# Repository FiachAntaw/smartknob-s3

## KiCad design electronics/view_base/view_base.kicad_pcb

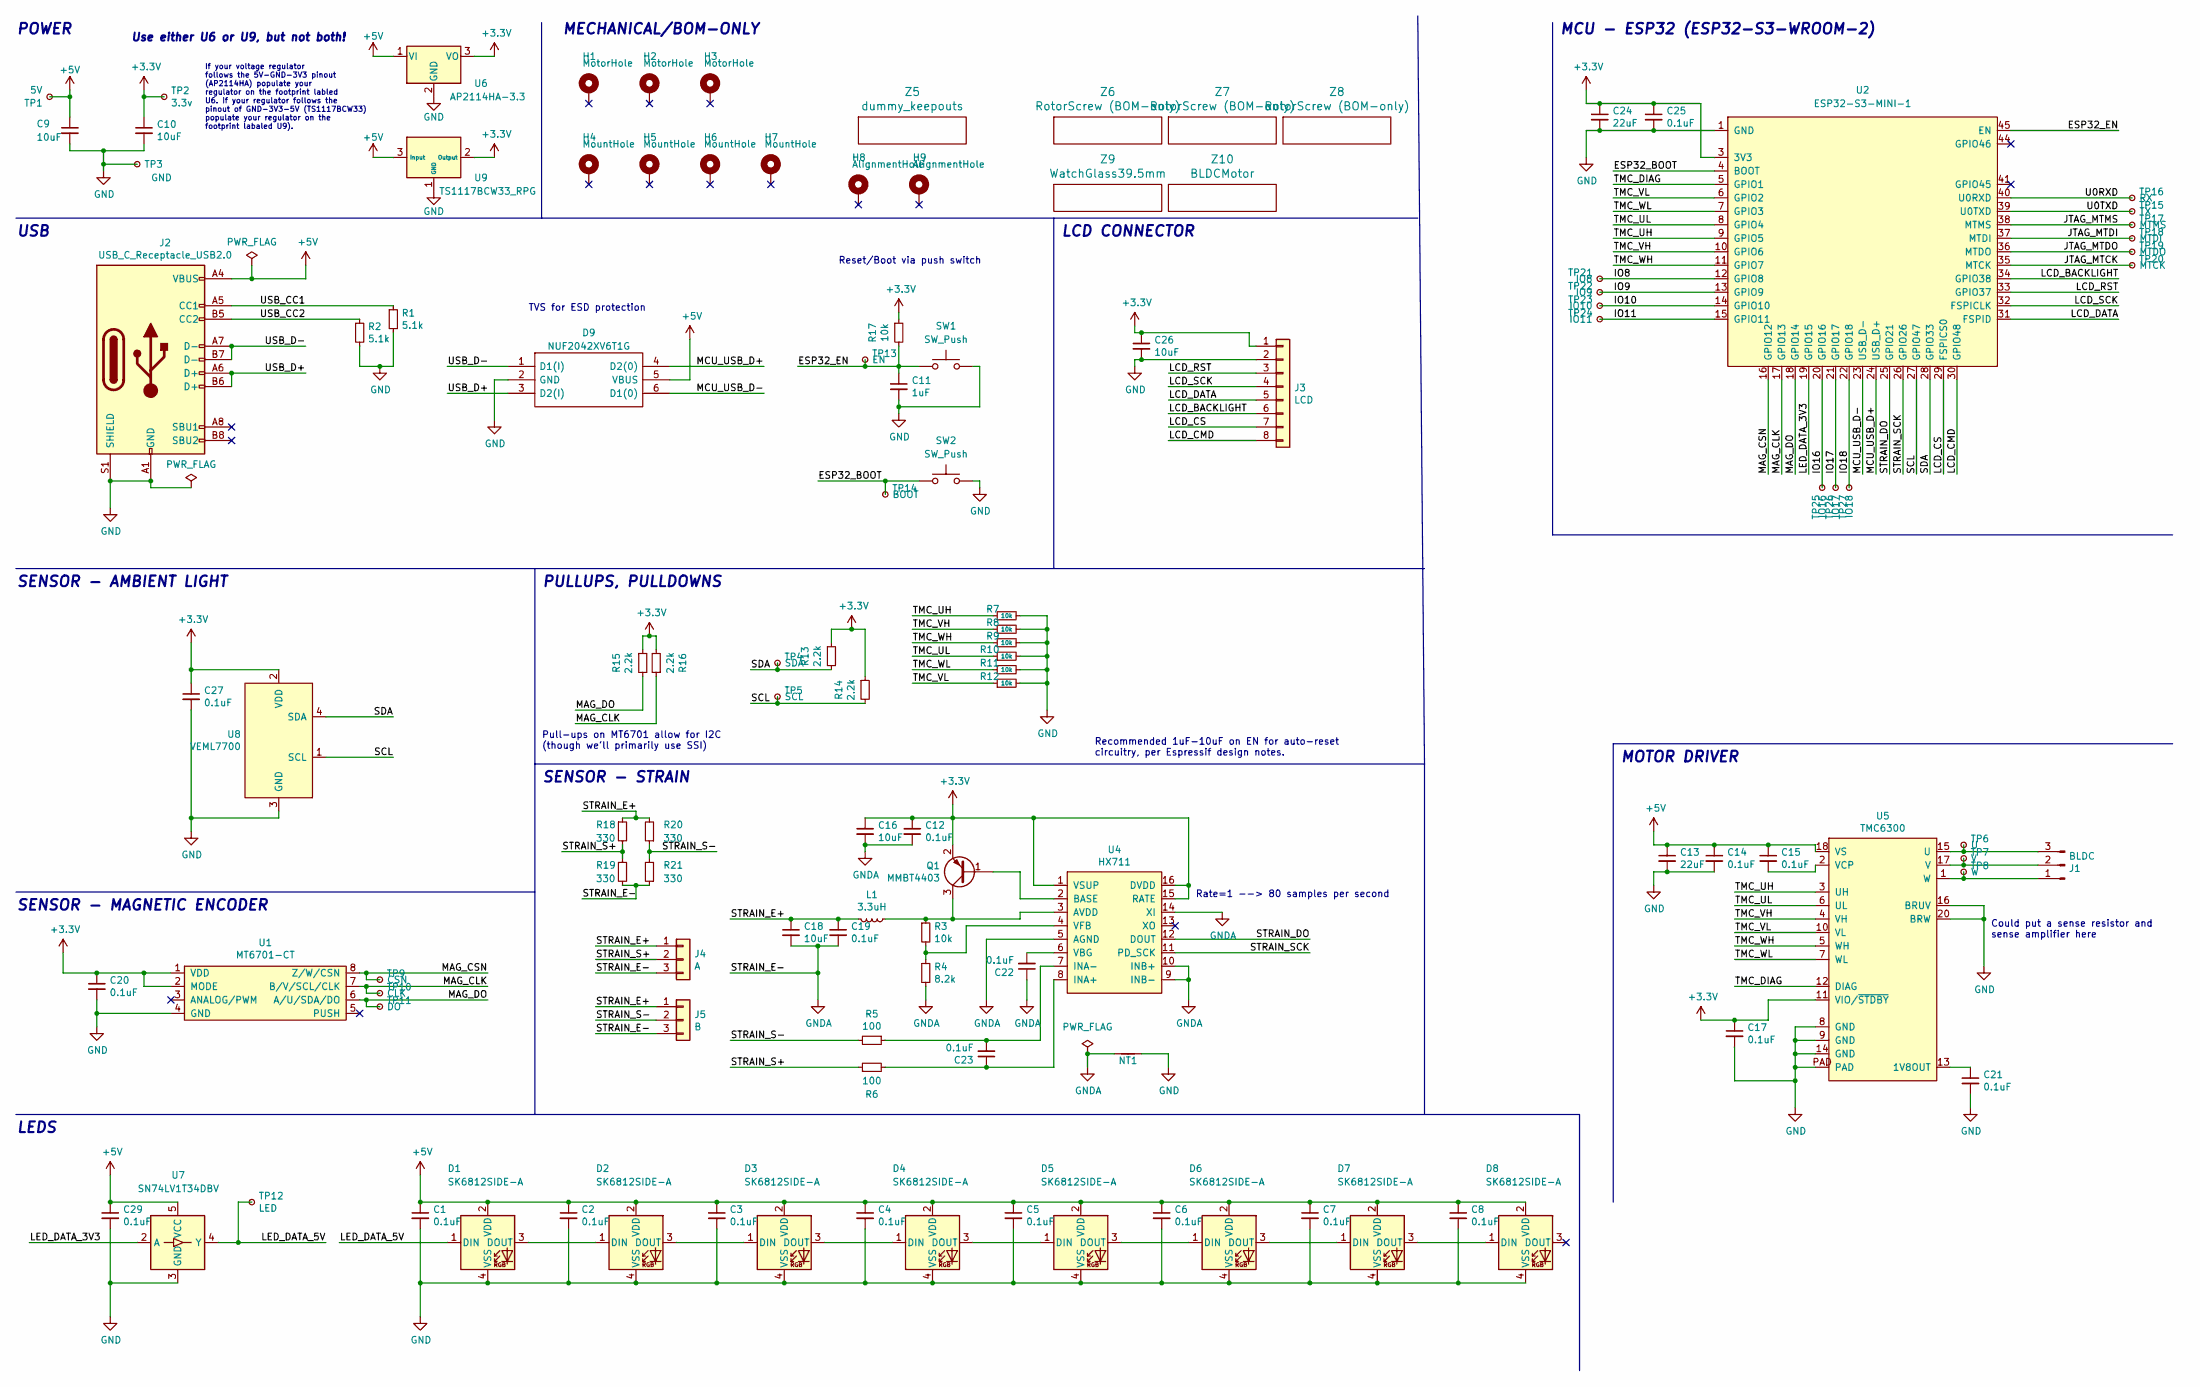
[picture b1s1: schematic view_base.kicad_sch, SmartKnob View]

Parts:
C1, C2, C3, C4, C5, C6, C7, C8, C12, C14, C15, C17, C19, C20, C21, C22, C23, C25, C27, C29: 0.1uF; C_0603_1608Metric; LCSC C1591
C9, C10, C16, C18, C26: 10uF; C_0805_2012Metric; LCSC C2922480
C11: 1uF; C_0603_1608Metric; Mouser 187-CL10A105KA8NNNC
C13, C24: 22uF; C_0805_2012Metric; LCSC C98190
D1, D2, D3, D4, D5, D6, D7, D8: SK6812SIDE-A; SK6812-SIDE-A; Digikey 1528-4691-ND
D9: NUF2042XV6T1G; SOT-563; Mouser Part Number 863-NUF2042XV6T1G
H1, H2, H3: MotorHole; MountingHole_M1.6; LCSC C2931389
H4, H5, H6, H7: MountHole; MountingHole_2.2mm_M2_ISO7380_Pad_NonVirtual; LCSC C2911210 or C2911532 (screw), C2961595 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
H8, H9: AlignmentHole; MountingHole_2.2mm_M2_ISO7380_Pad_NonVirtual
J1: BLDC; 532610371; LCSC C293630
J2: USB_C_Receptacle_USB2.0; USB4510_NoPaste; LCSC C428463
J3: LCD; SolderPads_2mm_8
J4: A; SolderPads_2mm_3_STRAIN
J5: B; SolderPads_2mm_3_STRAIN
L1: 3.3uH; L_0805_2012Metric; LCSC C307744
NT1: NetTie_2; NetTie-2_SMD_Pad0.5mm
Q1: MMBT4403; SOT-23; LCSC C78864
R1, R2: 5.1k; R_0603_1608Metric; LCSC C105580
R3, R7, R8, R9, R10, R11, R12, R17: 10k; R_0603_1608Metric; LCSC C98220
R4: 8.2k; R_0603_1608Metric; LCSC C114637
R5, R6: 100; R_0603_1608Metric; LCSC C319953
R13, R14, R15, R16: 2.2k; R_0603_1608Metric; LCSC C4190
R18, R19, R20, R21: 330; R_2512_6332Metric; LCSC C19866
SW1, SW2: SW_Push; SW_SPST_B3U-3000P-B
TP1: 5V; TestPoint_Pad_D2.0mm_ValueSilk
TP2: 3.3v; TestPoint_Pad_D2.0mm_ValueSilk
TP3: GND; TestPoint_Pad_D2.0mm_ValueSilk
TP4: SDA; TestPoint_Pad_D2.0mm_ValueSilk
TP5: SCL; TestPoint_Pad_D2.0mm_ValueSilk
TP6: U; TestPoint_Pad_D2.0mm_ValueSilk
TP7: V; TestPoint_Pad_D2.0mm_ValueSilk
TP8: W; TestPoint_Pad_D2.0mm_ValueSilk
TP9: CSN; TestPoint_Pad_D2.0mm_ValueSilk
TP10: CLK; TestPoint_Pad_D2.0mm_ValueSilk
TP11: DO; TestPoint_Pad_D2.0mm_ValueSilk
TP12: LED; TestPoint_Pad_D2.0mm_ValueSilk
TP13: EN; TestPoint_Pad_D2.0mm_ValueSilk
TP14: BOOT; TestPoint_Pad_D2.0mm_ValueSilk
TP15: TX; TestPoint_Pad_D2.0mm_ValueSilk
TP16: RX; TestPoint_Pad_D2.0mm_ValueSilk
TP17: MTMS; TestPoint_Pad_D2.0mm_ValueSilk
TP18: MTDI; TestPoint_Pad_D2.0mm_ValueSilk
TP19: MTDO; TestPoint_Pad_D2.0mm_ValueSilk
TP20: MTCK; TestPoint_Pad_D2.0mm_ValueSilk
TP21: IO8; TestPoint_Pad_D2.0mm_ValueSilk
TP22: IO9; TestPoint_Pad_D2.0mm_ValueSilk
TP23: IO10; TestPoint_Pad_D2.0mm_ValueSilk
TP24: IO11; TestPoint_Pad_D2.0mm_ValueSilk
TP25: IO16; TestPoint_Pad_D2.0mm_ValueSilk
TP26: IO17; TestPoint_Pad_D2.0mm_ValueSilk
TP27: IO18; TestPoint_Pad_D2.0mm_ValueSilk
U1: MT6701-CT; SOIC-8_3.9x4.9mm_P1.27mm; LCSC C2856764, or C3003196
U2: ESP32-S3-MINI-1
U4: HX711; SOIC-16_3.9x9.9mm_P1.27mm; LCSC C43656
U5: TMC6300; QFN-20-1EP_3x3mm_P0.4mm_EP1.65x1.65mm_ThermalVias_LargerVia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; Digikey TMC6300-LA-T
U6: AP2114HA-3.3; SOT-223-3_TabPin2_InGndOut; LCSC C460314
U7: SN74LV1T34DBV; SOT-23-5; LCSC C100024
U8: VEML7700; VEML7700-TOP; Digikey VEML7700-TT
U9: TS1117BCW33_RPG; SOT-223-3_TabPin2_GndOutIn; LCSC C6186, C35879, or others
Z5: dummy_keepouts; ViewKeepouts3d
Z6, Z7, Z8: RotorScrew (BOM-only); bom_only_no_pin
Z9: WatchGlass39.5mm; bom_only_no_pin
Z10: BLDCMotor; bom_only_no_pin

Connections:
+3V3: C10.1, C12.1, C16.1, C17.1, C20.1, C24.1, C25.1, C26.1, C27.1, J3.1, Q1.2 (E), R13.1, R14.1, R15.1, R16.2, R17.1, TP2.1, U1.1 (VDD), U1.2 (MODE), U2.3 (3V3), U4.1 (VSUP), U4.15 (RATE), U4.16 (DVDD), U5.11 (VIO/~STDBY), U6.3 (VO), U8.2 (VDD), U9.2 (Output)
+5V: C1.1, C2.1, C3.1, C4.1, C5.1, C6.1, C7.1, C8.1, C9.1, C13.1, C14.1, C15.1, C29.1, D1.2 (VDD), D2.2 (VDD), D3.2 (VDD), D4.2 (VDD), D5.2 (VDD), D6.2 (VDD), D7.2 (VDD), D8.2 (VDD), D9.5 (VBUS), J2.A4 (VBUS), J2.A9 (VBUS), J2.B4 (VBUS), J2.B9 (VBUS), TP1.1, U5.18 (VS), U6.1 (VI), U7.5 (VCC), U9.3 (Input)
/ESP32_BOOT: SW2.1, TP14.1, U2.4 (BOOT)
/ESP32_EN: C11.1, R17.2, SW1.1, TP13.1, U2.45 (EN)
/IO8: TP21.1, U2.12 (GPIO8)
/IO9: TP22.1, U2.13 (GPIO9)
/IO10: TP23.1, U2.14 (GPIO10)
/IO11: TP24.1, U2.15 (GPIO11)
/IO16: TP25.1, U2.20 (GPIO16)
/IO17: TP26.1, U2.21 (GPIO17)
/IO18: TP27.1, U2.22 (GPIO18)
/JTAG_MTCK: TP20.1, U2.35 (MTCK)
/JTAG_MTDI: TP18.1, U2.37 (MTDI)
/JTAG_MTDO: TP19.1, U2.36 (MTDO)
/JTAG_MTMS: TP17.1, U2.38 (MTMS)
/LCD_BACKLIGHT: J3.6, U2.34 (GPIO38)
/LCD_CMD: J3.8, U2.30 (GPIO48)
/LCD_CS: J3.7, U2.29 (FSPICS0)
/LCD_DATA: J3.5, U2.31 (FSPID)
/LCD_RST: J3.3, U2.33 (GPIO37)
/LCD_SCK: J3.4, U2.32 (FSPICLK)
/LED_DATA_3V3: U2.19 (GPIO15), U7.2 (A)
/LED_DATA_5V: D1.1 (DIN), TP12.1, U7.4 (Y)
/MAG_CLK: R16.1, TP10.1, U1.7 (B/V/SCL/CLK), U2.17 (GPIO13)
/MAG_CSN: TP9.1, U1.8 (Z/W/CSN), U2.16 (GPIO12)
/MAG_DO: R15.2, TP11.1, U1.6 (A/U/SDA/DO), U2.18 (GPIO14)
/MCU_USB_D+: D9.4 (D2(0)), U2.24 (USB_D+)
/MCU_USB_D-: D9.6 (D1(0)), U2.23 (USB_D-)
/SCL: R14.2, TP5.1, U2.27 (GPIO47), U8.1 (SCL)
/SDA: R13.2, TP4.1, U2.28 (GPIO33), U8.4 (SDA)
/STRAIN_DO: U2.25 (GPIO21), U4.12 (DOUT)
/STRAIN_E+: C18.1, C19.1, J4.1, J5.1, L1.2, R18.1, R20.2
/STRAIN_S+: J4.2, R6.1, R18.2, R19.1
/STRAIN_S-: J5.2, R5.2, R20.1, R21.2
/STRAIN_SCK: U2.26 (GPIO26), U4.11 (PD_SCK)
/TMC_DIAG: U2.5 (GPIO1), U5.12 (DIAG)
/TMC_UH: R7.1, U2.9 (GPIO5), U5.3 (UH)
/TMC_UL: R10.1, U2.8 (GPIO4), U5.6 (UL)
/TMC_VH: R8.1, U2.10 (GPIO6), U5.4 (VH)
/TMC_VL: R12.1, U2.6 (GPIO2), U5.10 (VL)
/TMC_WH: R9.1, U2.11 (GPIO7), U5.5 (WH)
/TMC_WL: R11.1, U2.7 (GPIO3), U5.7 (WL)
/U0RXD: TP16.1, U2.40 (U0RXD)
/U0TXD: TP15.1, U2.39 (U0TXD)
/USB_CC1: J2.A5 (CC1), R1.1
/USB_CC2: J2.B5 (CC2), R2.1
/USB_D+: D9.3 (D2(I)), J2.A6 (D+), J2.B6 (D+)
/USB_D-: D9.1 (D1(I)), J2.A7 (D-), J2.B7 (D-)
GND: C1.2, C2.2, C3.2, C4.2, C5.2, C6.2, C7.2, C8.2, C9.2, C10.2, C11.2, C13.2, C14.2, C17.2, C20.2, C21.2, C24.2, C25.2, C26.2, C27.2, C29.2, D1.4 (VSS), D2.4 (VSS), D3.4 (VSS), D4.4 (VSS), D5.4 (VSS), D6.4 (VSS), D7.4 (VSS), D8.4 (VSS), D9.2 (GND), J2.A1 (GND), J2.A12 (GND), J2.B1 (GND), J2.B12 (GND), J2.S1 (SHIELD), J3.2, NT1.2, R1.2, R2.2, R7.2, R8.2, R9.2, R10.2, R11.2, R12.2, SW1.2, SW2.2, TP3.1, U1.4 (GND), U2.1 (GND), U2.2 (GND), U2.42 (GND), U2.43 (GND), U2.46 (GND), U2.47 (GND), U2.48 (GND), U2.49 (GND), U2.50 (GND), U2.51 (GND), U2.52 (GND), U2.53 (GND), U2.54 (GND), U2.55 (GND), U2.56 (GND), U2.57 (GND), U2.58 (GND), U2.59 (GND), U2.60 (GND), U2.61 (GND), U2.62 (GND), U2.63 (GND), U2.64 (GND), U2.65 (GND), U5.8 (GND), U5.9 (GND), U5.14 (GND), U5.16 (BRUV), U5.20 (BRW), U5.PAD, U6.2 (GND), U7.3 (GND), U8.3 (GND), U9.1 (GND)
GNDA: C12.2, C16.2, C18.2, C19.2, C22.1, J4.3, J5.3, NT1.1, R4.2, R19.2, R21.1, U4.5 (AGND), U4.9 (INB-), U4.10 (INB+), U4.14 (XI)
unnamed: D1.3 (DOUT), D2.1 (DIN)
unnamed: D2.3 (DOUT), D3.1 (DIN)
unnamed: D3.3 (DOUT), D4.1 (DIN)
unnamed: D4.3 (DOUT), D5.1 (DIN)
unnamed: D5.3 (DOUT), D6.1 (DIN)
unnamed: D6.3 (DOUT), D7.1 (DIN)
unnamed: D7.3 (DOUT), D8.1 (DIN)
unnamed: J1.1, TP8.1, U5.1 (W)
unnamed: J1.2, TP7.1, U5.17 (V)
unnamed: J1.3, TP6.1, U5.15 (U)
unnamed: Q1.1 (B), U4.2 (BASE)
unnamed: L1.1, Q1.3 (C), R3.1, U4.3 (AVDD)
unnamed: C23.1, R6.2, U4.8 (INA+)
unnamed: C23.2, R5.1, U4.7 (INA-)
unnamed: C22.2, U4.6 (VBG)
unnamed: R3.2, R4.1, U4.4 (VFB)
unnamed: C21.1, U5.13 (1V8OUT)
unnamed: C15.2, U5.2 (VCP)

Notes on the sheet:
TVS for ESD protection
POWER
Could put a sense resistor and sense amplifier here
MCU - ESP32 (ESP32-S3-WROOM-2)
If your voltage regulator follows the 5V-GND-3V3 pinout (AP2114HA) populate your regulator on the footprint labled U6. If your regulator follows the pinout of GND-3V3-5V (TS1117BCW33) populate your regulator on the footprint labaled U9).
SENSOR - MAGNETIC ENCODER
MOTOR DRIVER
MECHANICAL/BOM-ONLY
Pull-ups on MT6701 allow for I2C (though we'll primarily use SSI)
Use either U6 or U9, but not both!
Rate=1 --> 80 samples per second
SENSOR - AMBIENT LIGHT
Recommended 1uF-10uF on EN for auto-reset circuitry, per Espressif design notes.
USB
SENSOR - STRAIN
LEDS
PULLUPS, PULLDOWNS
LCD CONNECTOR
Reset/Boot via push switch

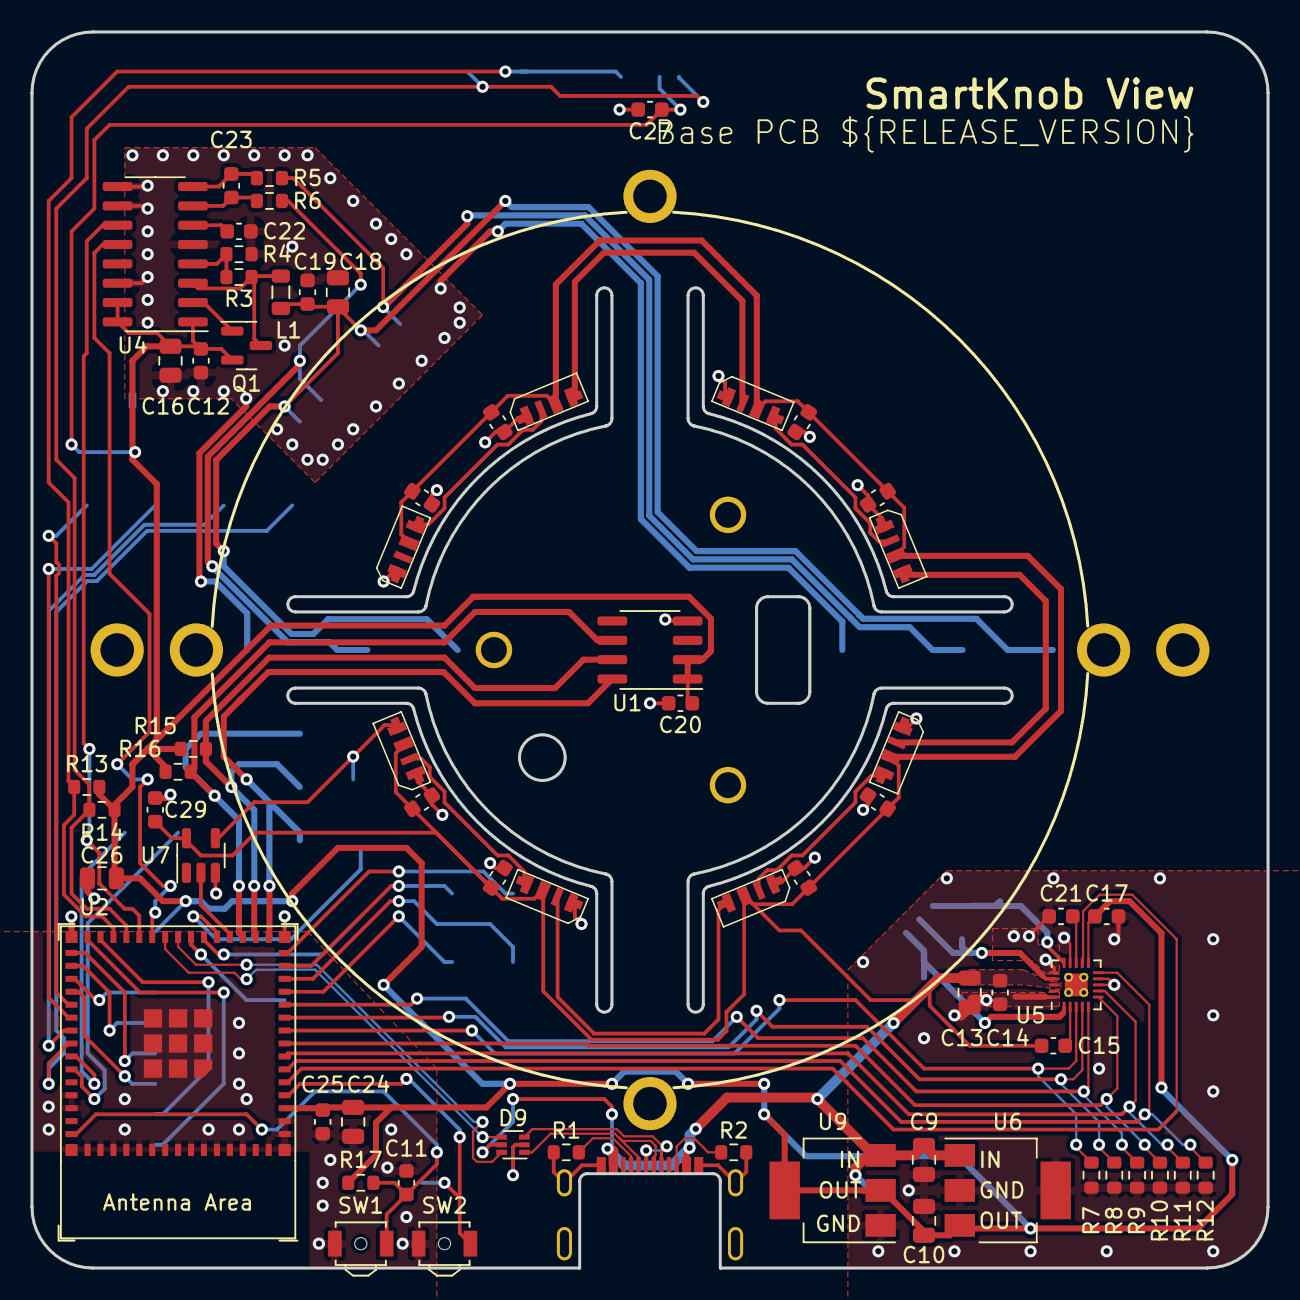
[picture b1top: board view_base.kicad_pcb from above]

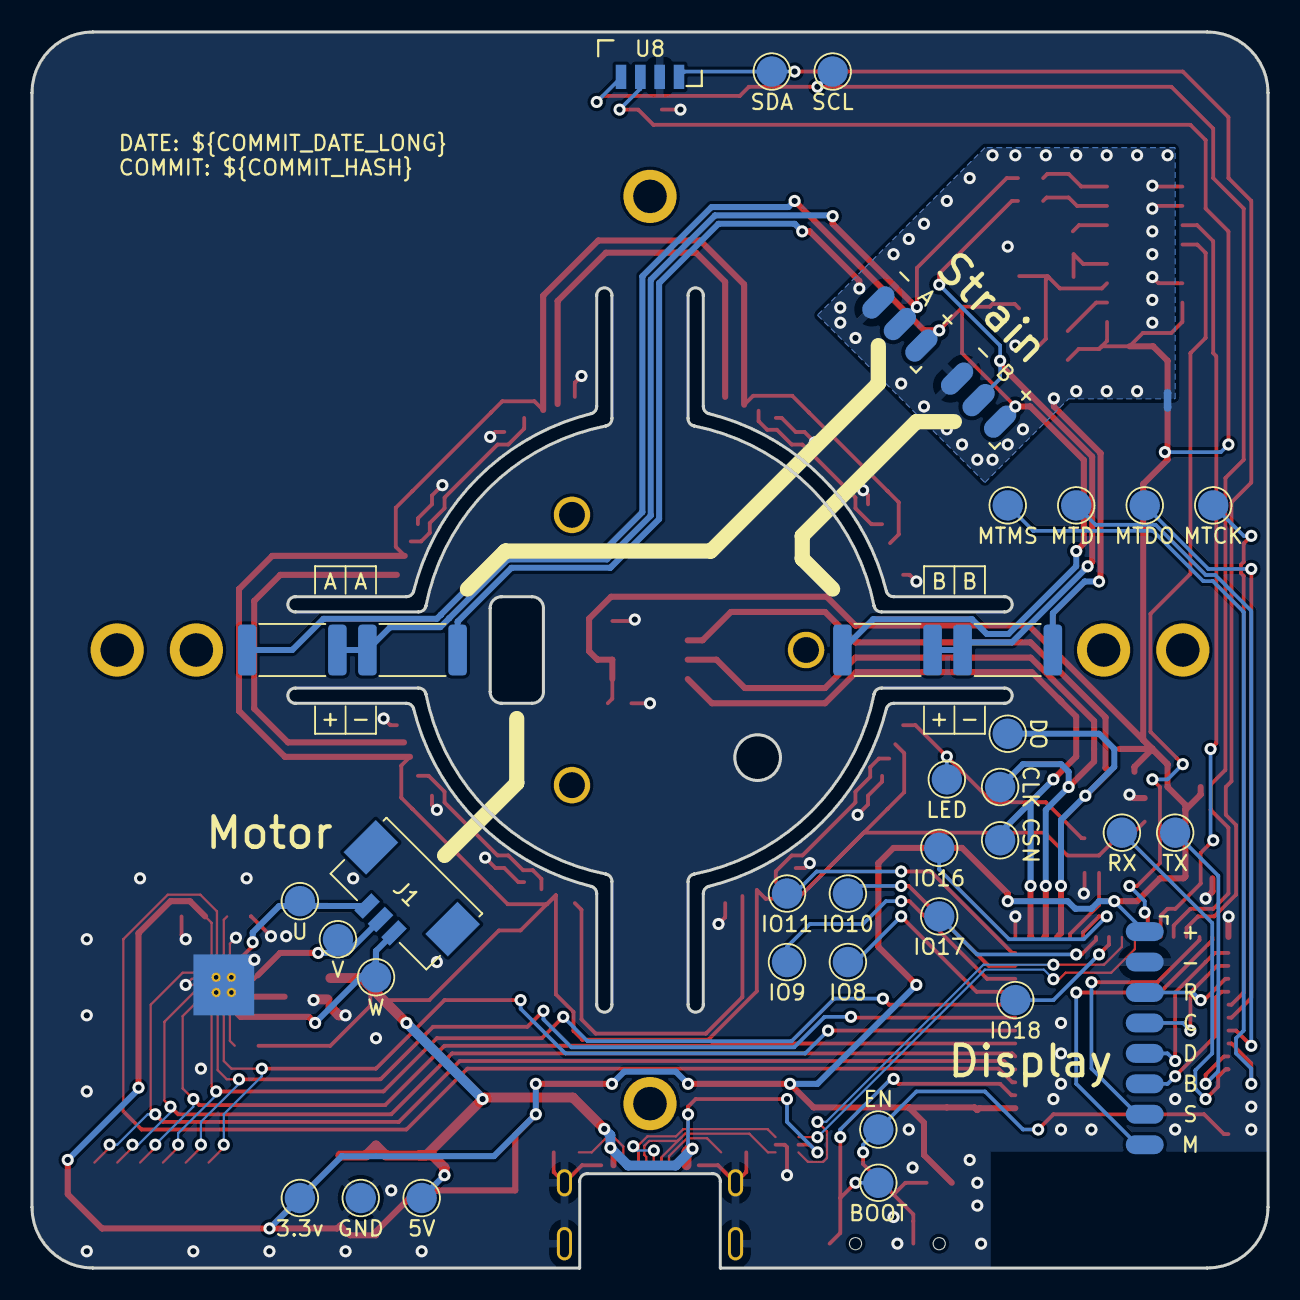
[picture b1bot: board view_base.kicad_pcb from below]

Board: 2 copper layers, 81.2 x 81.2 mm, 118 parts (37 on the bottom side), 68 nets.

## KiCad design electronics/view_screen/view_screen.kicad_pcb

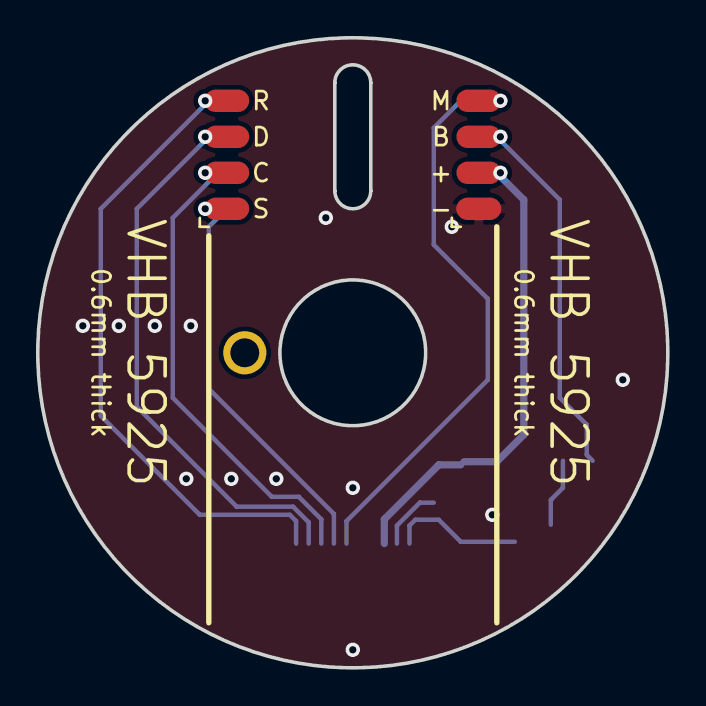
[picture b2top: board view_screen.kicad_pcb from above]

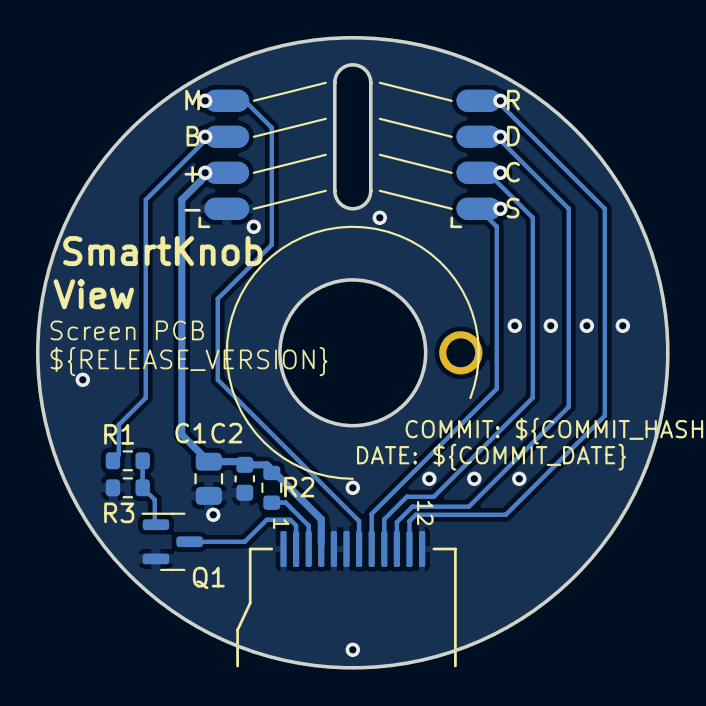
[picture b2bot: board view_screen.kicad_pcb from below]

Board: 2 copper layers, 35.0 x 35.0 mm, 12 parts (9 on the bottom side), 11 nets.

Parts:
C1: 22uF; C_0805_2012Metric
C2: 0.1uF; C_0603_1608Metric
H1: AlignmentHole; AlignmentHole_1.6
J1, J3, J4, J5: Conn_01x04; SolderPads_2mm_4
J2: GC9A01; GC9A01Round1.28
Q1: 2N7002; SOT-23
R1: 10k; R_0603_1608Metric
R2: 22R; R_0603_1608Metric
R3: 1M; R_0603_1608Metric

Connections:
/BACKLIGHT_EN: J1.3, J4.3, R1.1
/DC: J1.4, J2.7, J4.4
/LEDA: J2.3, R2.2
/LEDK: J2.2, Q1.3 (D)
/MOSI: J2.10, J3.3, J5.3
/SCK: J2.9, J3.2, J5.2
/VDD: C1.1, C2.1, J1.2, J2.4, J4.2, R2.1
/nCS: J2.8, J3.1, J5.1
/nRESET: J2.11, J3.4, J5.4
GND: C1.2, C2.2, J1.1, J2.1, J2.5, J2.6, J2.12, J4.1, Q1.2 (S), R3.2
unnamed: Q1.1 (G), R1.2, R3.1

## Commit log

2023-09-06 Use ESP32-S3-MINI-1 in place of TMicro32 Plus
2023-09-06 Configure HX711 pins in platformio.ini
2023-09-06 Add S3 configuration to platformio.ini
2023-09-06 Lower LEDC backlight resolution/frequency for S3
2023-09-06 Change MT6701 SPI channel for S3

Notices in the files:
parts and their libraries:
Copyright 2021 Accelerated Designs. All rights reserved.
